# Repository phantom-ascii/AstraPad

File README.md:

# ✦ AstraPad

> REVIWERS THIS WAS NOT MADE BY AI THXXX
> A tiny macropad for a very specific Linux problem.

**Stardance:** https://stardance.hackclub.com/@phantom-ascii/

---

## What is AstraPad?

If you've used the Linux terminal, you've probably noticed that `Ctrl + C` and `Ctrl + V` don't work like they do everywhere else.

Instead:

- `Ctrl + Shift + C` → Copy
- `Ctrl + Shift + V` → Paste

It's not a massive problem, but when you're using the terminal constantly, reaching for that extra `Shift` gets annoying.

So I decided to build a little hardware solution.

**AstraPad** is a custom 4-key macropad designed around Linux terminal shortcuts, with two rotary encoders and an OLED display.

### Features

- 4 programmable shortcut keys
- 2 rotary encoders
- OLED status display
- Seeed XIAO RP2040
- Custom PCB
- Custom 3D-printed case
- Volume and mute control
- Brightness control
- Custom KMK firmware

---

## Keymap

| Control | Function |
|---|---|
| SW1 | `Ctrl + Shift + C` |
| SW2 | `Ctrl + Shift + V` |
| SW3 | `Ctrl + C` |
| SW4 | `Ctrl + V` |
| ROT1 clockwise | Volume up |
| ROT1 counter-clockwise | Volume down |
| ROT1 press | Mute |
| ROT2 clockwise | Brightness up |
| ROT2 counter-clockwise | Brightness down |

The planned OLED behaviour is to display the current volume or brightness while it is being adjusted, then turn off after 1 second of inactivity.

---

## Hardware

### PCB

The PCB was designed and routed from scratch in **KiCad**.

The board is designed around:

- Seeed XIAO RP2040
- 4 direct-wired switches
- 2 rotary encoders
- I²C OLED
- USB-C
- Custom PCB mounting points

The PCB has been through a KiCad DRC with **0 unconnected pads**.

### Schematic

The schematic contains the electrical design and pin assignments for AstraPad.

### Pinout

#### Switches

| Component | XIAO Pin |
|---|---|
| SW1 | D0 |
| SW2 | D1 |
| SW3 | D2 |
| SW4 | D3 |

#### OLED

| Signal | XIAO Pin |
|---|---|
| SDA | D4 |
| SCL | D5 |

#### ROT1

| Signal | XIAO Pin |
|---|---|
| A | D6 |
| B | D7 |
| Push | D8 |

#### ROT2

| Signal | XIAO Pin |
|---|---|
| A | D9 |
| B | D10 |

ROT2 does not have a push switch.

---

## Case

The case was designed from scratch in **FreeCAD**.

It consists of:

- Top lid
- Bottom tray
- Custom PCB mounting pillars
- USB-C access
- OLED opening
- Switch openings
- Rotary encoder openings

The PCB sits directly inside the bottom tray using custom-designed mounting pillars.

### Exploded View

The exploded view shows how the PCB and case fit together.

The case was designed around the PCB rather than being an afterthought.

---

## Project Files

The repository contains the source files required to reproduce the design.

### PCB

The repository contains:

- KiCad project files
- KiCad schematic
- KiCad PCB layout
- Gerbers

### CAD

The repository contains:

- FreeCAD `.FCStd` source files
- Master assembly
- `.STEP` assembly
- Top case
- Bottom case

### Firmware

Firmware is being developed using **KMK** and **CircuitPython**.

The firmware is currently a work in progress and will be tested once the XIAO RP2040 arrives.

---

## Bill of Materials

See [`BOM.csv`](./BOM.csv) for the current bill of materials and project requirements.

The Hackpad Kit provides the main electronic components used by AstraPad.

Additional requirements include PCB manufacturing and a soldering iron.

---

## Building It

I'm designing everything from scratch using **KiCad** and **FreeCAD**, then writing the firmware with the help of AI.

This is my first proper PCB project, so things will probably break.

That's part of it.

I've already had to redesign parts of the PCB after realising that I had the USB-C connector facing the wrong direction.

Turns out designing hardware is slightly less forgiving than writing HTML.

---

## Progress

### Design

- [x] Schematic
- [x] PCB layout
- [x] PCB DRC
- [x] Case design
- [x] PCB mounting
- [x] USB-C case opening
- [x] Gerbers
- [x] KiCad source files
- [x] FreeCAD source files
- [x] Master STEP assembly
- [x] BOM
- [x] GitHub repository
- [x] Initial firmware

### Remaining

- [ ] Finish firmware
- [ ] Sanity check
- [ ] Order parts
- [ ] Assemble
- [ ] First power-on
- [ ] Test keys, encoders and OLED
- [ ] Final build
- [ ] Ship

---

## Devlog

I'm documenting the build and the problems I run into on Stardance.

**Devlog:**  
https://stardance.hackclub.com/@phantom-ascii/

The build hasn't exactly gone smoothly.

I've already had to redesign the PCB after discovering that the USB-C connector was facing into the PCB instead of out through the case.

But that's kind of the point.

I'm learning by actually building something.

---

## About

Made by `phantom-ascii`

14yo learning Linux, hardware, PCB design and embedded development.

Trying to turn annoying little problems into actual things.

---
## Status

**Building**

The hardware design is complete.

AstraPad is now moving into firmware, manufacturing, assembly and testing.

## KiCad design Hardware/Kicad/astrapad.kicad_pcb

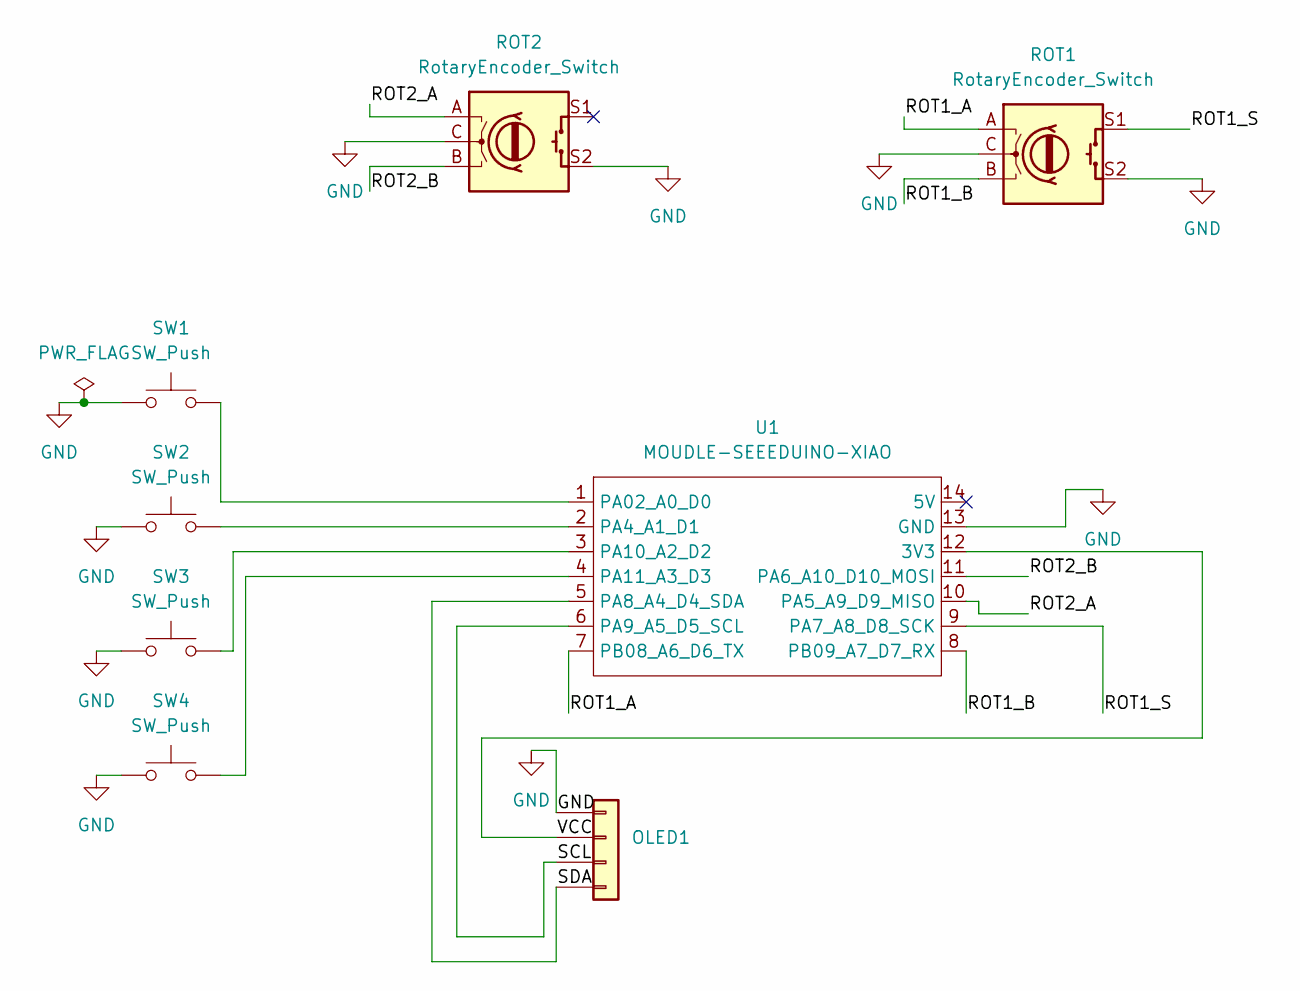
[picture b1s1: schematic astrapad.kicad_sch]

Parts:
OLED1: PinHeader_1x04_P2.54mm_Vertical
ROT1, ROT2: RotaryEncoder_Switch; RotaryEncoder_Alps_EC11E-Switch_Vertical_H20mm
SW1, SW2, SW3, SW4: SW_Push; SW_Cherry_MX_1.00u_PCB
U1: MOUDLE-SEEEDUINO-XIAO; XIAO-Generic-Hybrid-14P-2.54-21X17.8MM

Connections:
/ROT1_A: ROT1.A, U1.7 (PB08_A6_D6_TX)
/ROT1_B: ROT1.B, U1.8 (PB09_A7_D7_RX)
/ROT1_S: ROT1.S1, U1.9 (PA7_A8_D8_SCK)
/ROT2_A: ROT2.A, U1.10 (PA5_A9_D9_MISO)
/ROT2_B: ROT2.B, U1.11 (PA6_A10_D10_MOSI)
/SCL: OLED1.3, U1.6 (PA9_A5_D5_SCL)
/SDA: OLED1.4, U1.5 (PA8_A4_D4_SDA)
/VCC: OLED1.2, U1.12 (3V3)
GND: OLED1.1, ROT1.C, ROT1.S2, ROT2.C, ROT2.S2, SW1.1, SW2.1, SW3.1, SW4.1, U1.13 (GND)
unnamed: SW1.2, U1.1 (PA02_A0_D0)
unnamed: SW2.2, U1.2 (PA4_A1_D1)
unnamed: SW3.2, U1.3 (PA10_A2_D2)
unnamed: SW4.2, U1.4 (PA11_A3_D3)

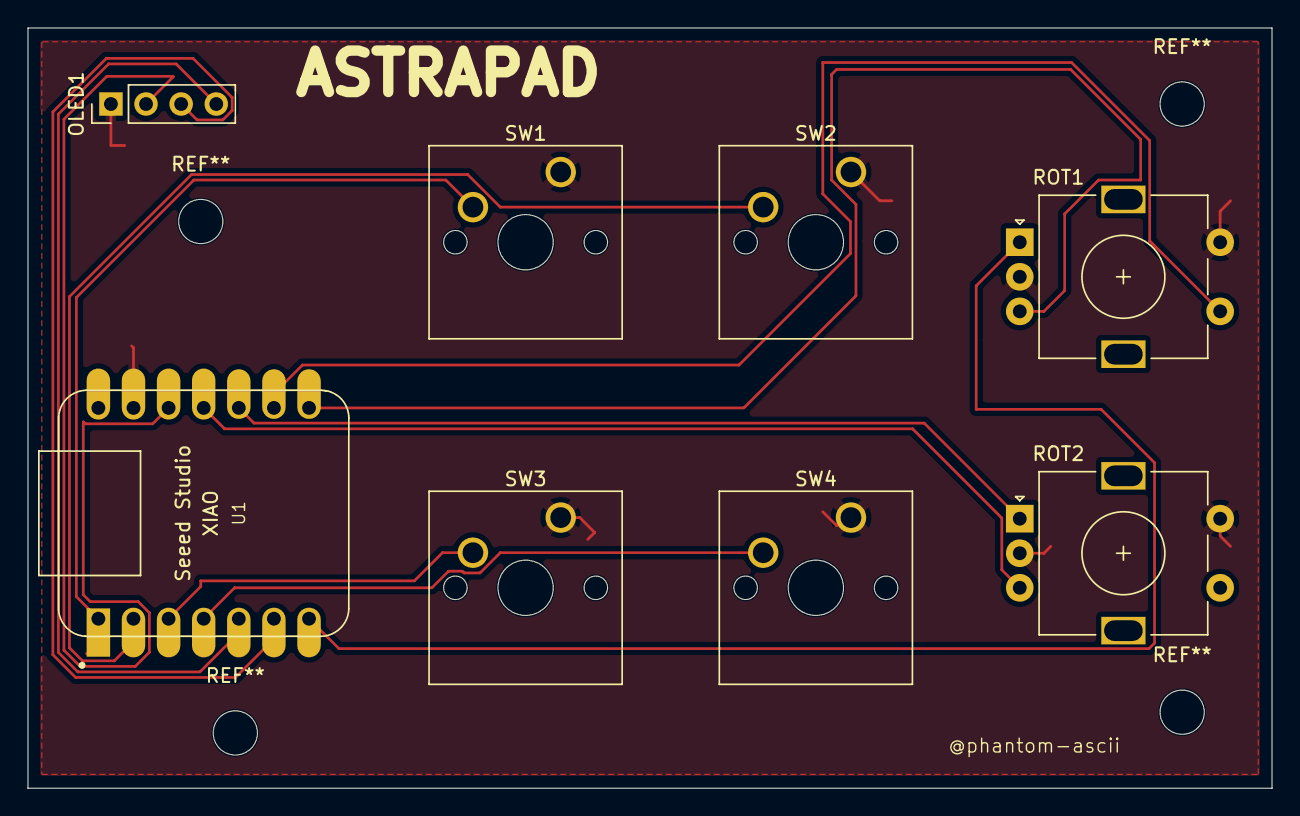
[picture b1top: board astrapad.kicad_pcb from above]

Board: 2 copper layers, 90.0 x 55.0 mm, 8 parts (0 on the bottom side), 13 nets.
